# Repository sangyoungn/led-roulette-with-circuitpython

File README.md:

# LED Roulette with CircuitPython

This is a project to build an LED roulette with CircuitPython on EFR32xG24 Explorer Kit.

## Contents

"**hardware**" directory contains files for the hardware design including schematic and gerber output.
"**code**" directry contains scripts written in CircuitPython, which run on EFR32xG24 Explorer Kit.

## Directory Structure

.   
├── **hardware**   
|&nbsp;&nbsp;&nbsp;&nbsp;&nbsp;└── **roulette** (KiCad Design Directory)   
|&nbsp;&nbsp;&nbsp;&nbsp;&nbsp;&nbsp;&nbsp;&nbsp;&nbsp;&nbsp;├── **gerber** (PCB Gerber Plot Directory)   
|&nbsp;&nbsp;&nbsp;&nbsp;&nbsp;&nbsp;&nbsp;&nbsp;&nbsp;&nbsp;├── **pdf** (PCB PDF Polt Directory)   
|&nbsp;&nbsp;&nbsp;&nbsp;&nbsp;&nbsp;&nbsp;&nbsp;&nbsp;&nbsp;├── *roulette.dxf* (PCB Outline and Decoration Silk DXF)   
|&nbsp;&nbsp;&nbsp;&nbsp;&nbsp;&nbsp;&nbsp;&nbsp;&nbsp;&nbsp;├── *roulette.kicad_pcb* (PCB Design File)   
|&nbsp;&nbsp;&nbsp;&nbsp;&nbsp;&nbsp;&nbsp;&nbsp;&nbsp;&nbsp;├── *roulette.kicad_pro* (KiCad Project File)   
|&nbsp;&nbsp;&nbsp;&nbsp;&nbsp;&nbsp;&nbsp;&nbsp;&nbsp;&nbsp;├── *roulette.pdf* (PDF Plot File of Whole Schematic)   
|&nbsp;&nbsp;&nbsp;&nbsp;&nbsp;&nbsp;&nbsp;&nbsp;&nbsp;&nbsp;├── *roulette.kicad_sch* (Schematic File #1)   
|&nbsp;&nbsp;&nbsp;&nbsp;&nbsp;&nbsp;&nbsp;&nbsp;&nbsp;&nbsp;├── *LEDs.kicad_sch* (Schematic File #2)    
|&nbsp;&nbsp;&nbsp;&nbsp;&nbsp;&nbsp;&nbsp;&nbsp;&nbsp;&nbsp;└── *xg24_explorer_kit.kicad_sch* (Schematic File #3)   
└── **code**   
&nbsp;&nbsp;&nbsp;&nbsp;&nbsp;├── *code.py*   
&nbsp;&nbsp;&nbsp;&nbsp;&nbsp;└── *led_roulette.py*   

Refer to clips in the link for more information.

https://youtube.com/playlist?list=PLlT0qmKc0_5ddENmn3fNbMIVXvFqQTv2Z&si=PHfeczIfOtfNPaJ8

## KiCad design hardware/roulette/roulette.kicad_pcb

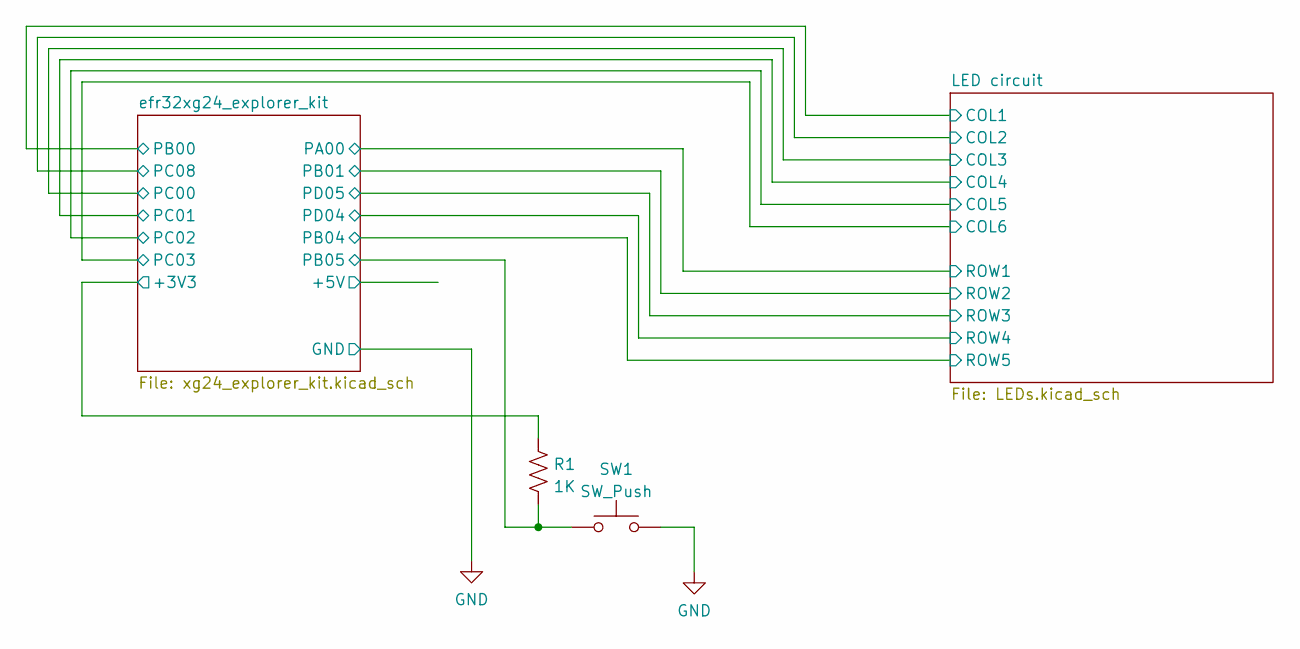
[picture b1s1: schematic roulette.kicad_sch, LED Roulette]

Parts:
R1: 1K; R_Axial_DIN0207_L6.3mm_D2.5mm_P7.62mm_Horizontal
SW1: SW_Push; SW_PUSH_6mm

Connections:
+3V3: R1.1; also elsewhere on the board
/efr32xg24_explorer_kit/PB05: R1.2, SW1.1; also elsewhere on the board
GND: SW1.2; also elsewhere on the board

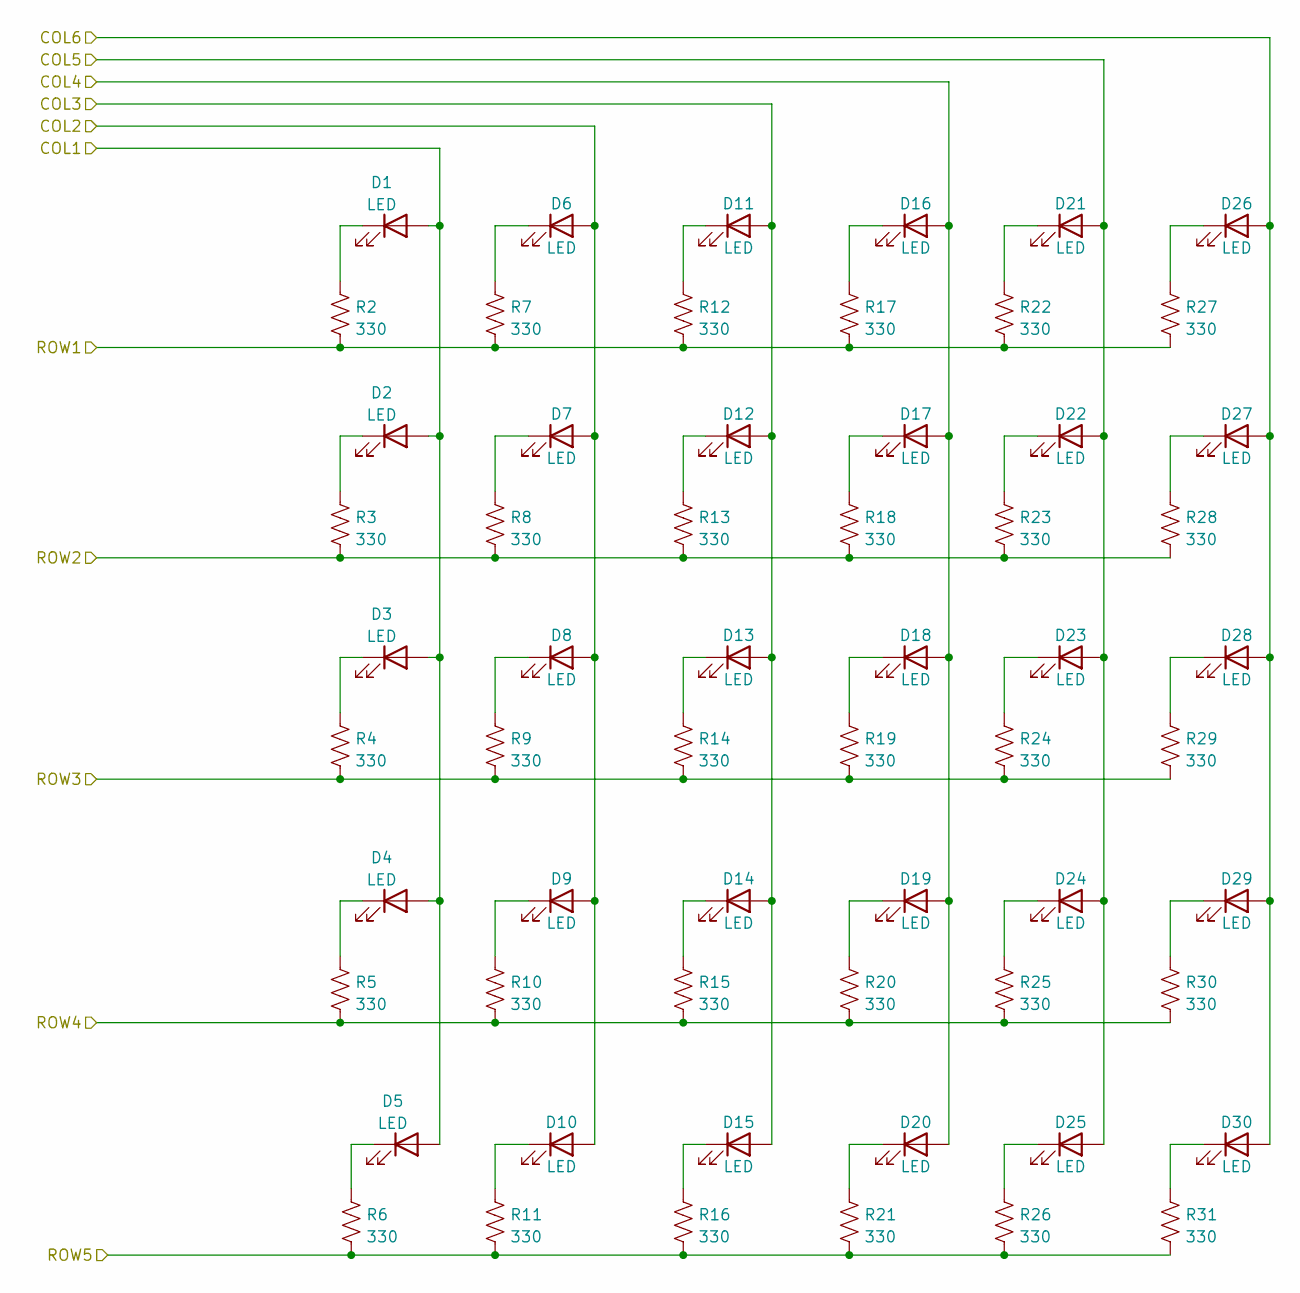
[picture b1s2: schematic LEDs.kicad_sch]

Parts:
D1, D2, D3, D4, D5, D6, D7, D8, D9, D10, D11, D12, D13, D14, D15, D16, D17, D18, D19, D20, D21, D22, D23, D24, D25, D26, D27, D28, D29, D30: LED; LED_D5.0mm
R2, R3, R4, R5, R6, R7, R8, R9, R10, R11, R12, R13, R14, R15, R16, R17, R18, R19, R20, R21, R22, R23, R24, R25, R26, R27, R28, R29, R30, R31: 330; R_Axial_DIN0207_L6.3mm_D2.5mm_P7.62mm_Horizontal

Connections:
/efr32xg24_explorer_kit/PA00: R2.2, R7.2, R12.2, R17.2, R22.2, R27.2; also elsewhere on the board
/efr32xg24_explorer_kit/PB00: D1.2 (A), D2.2 (A), D3.2 (A), D4.2 (A), D5.2 (A); also elsewhere on the board
/efr32xg24_explorer_kit/PB01: R3.2, R8.2, R13.2, R18.2, R23.2, R28.2; also elsewhere on the board
/efr32xg24_explorer_kit/PB04: R6.2, R11.2, R16.2, R21.2, R26.2, R31.2; also elsewhere on the board
/efr32xg24_explorer_kit/PC00: D11.2 (A), D12.2 (A), D13.2 (A), D14.2 (A), D15.2 (A); also elsewhere on the board
/efr32xg24_explorer_kit/PC01: D16.2 (A), D17.2 (A), D18.2 (A), D19.2 (A), D20.2 (A); also elsewhere on the board
/efr32xg24_explorer_kit/PC02: D21.2 (A), D22.2 (A), D23.2 (A), D24.2 (A), D25.2 (A); also elsewhere on the board
/efr32xg24_explorer_kit/PC03: D26.2 (A), D27.2 (A), D28.2 (A), D29.2 (A), D30.2 (A); also elsewhere on the board
/efr32xg24_explorer_kit/PC08: D6.2 (A), D7.2 (A), D8.2 (A), D9.2 (A), D10.2 (A); also elsewhere on the board
/efr32xg24_explorer_kit/PD04: R5.2, R10.2, R15.2, R20.2, R25.2, R30.2; also elsewhere on the board
/efr32xg24_explorer_kit/PD05: R4.2, R9.2, R14.2, R19.2, R24.2, R29.2; also elsewhere on the board
unnamed: D1.1 (K), R2.1
unnamed: D2.1 (K), R3.1
unnamed: D3.1 (K), R4.1
unnamed: D4.1 (K), R5.1
unnamed: D5.1 (K), R6.1
unnamed: D6.1 (K), R7.1
unnamed: D7.1 (K), R8.1
unnamed: D8.1 (K), R9.1
unnamed: D9.1 (K), R10.1
unnamed: D10.1 (K), R11.1
unnamed: D11.1 (K), R12.1
unnamed: D12.1 (K), R13.1
unnamed: D13.1 (K), R14.1
unnamed: D14.1 (K), R15.1
unnamed: D15.1 (K), R16.1
unnamed: D16.1 (K), R17.1
unnamed: D17.1 (K), R18.1
unnamed: D18.1 (K), R19.1
unnamed: D19.1 (K), R20.1
unnamed: D20.1 (K), R21.1
unnamed: D21.1 (K), R22.1
unnamed: D22.1 (K), R23.1
unnamed: D23.1 (K), R24.1
unnamed: D24.1 (K), R25.1
unnamed: D25.1 (K), R26.1
unnamed: D26.1 (K), R27.1
unnamed: D27.1 (K), R28.1
unnamed: D28.1 (K), R29.1
unnamed: D29.1 (K), R30.1
unnamed: D30.1 (K), R31.1

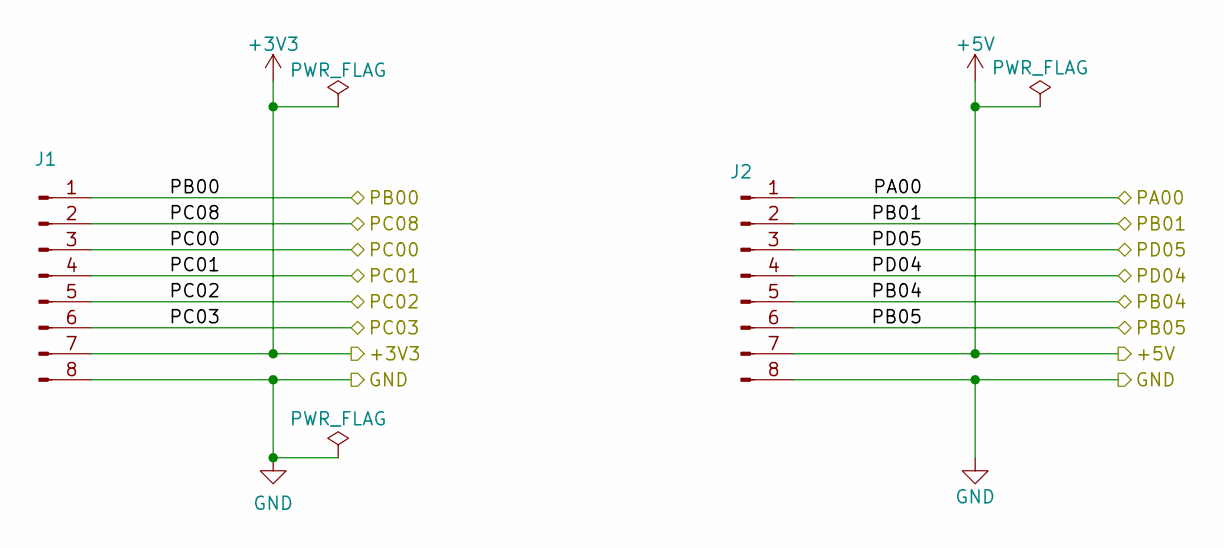
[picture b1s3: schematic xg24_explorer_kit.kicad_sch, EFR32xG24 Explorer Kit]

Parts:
J1, J2: Conn_01x08_Male; PinHeader_1x08_P2.54mm_Vertical

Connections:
+3V3: J1.7; also elsewhere on the board
+5V: J2.7
/efr32xg24_explorer_kit/PA00: J2.1; also elsewhere on the board
/efr32xg24_explorer_kit/PB00: J1.1; also elsewhere on the board
/efr32xg24_explorer_kit/PB01: J2.2; also elsewhere on the board
/efr32xg24_explorer_kit/PB04: J2.5; also elsewhere on the board
/efr32xg24_explorer_kit/PB05: J2.6; also elsewhere on the board
/efr32xg24_explorer_kit/PC00: J1.3; also elsewhere on the board
/efr32xg24_explorer_kit/PC01: J1.4; also elsewhere on the board
/efr32xg24_explorer_kit/PC02: J1.5; also elsewhere on the board
/efr32xg24_explorer_kit/PC03: J1.6; also elsewhere on the board
/efr32xg24_explorer_kit/PC08: J1.2; also elsewhere on the board
/efr32xg24_explorer_kit/PD04: J2.4; also elsewhere on the board
/efr32xg24_explorer_kit/PD05: J2.3; also elsewhere on the board
GND: J1.8, J2.8; also elsewhere on the board

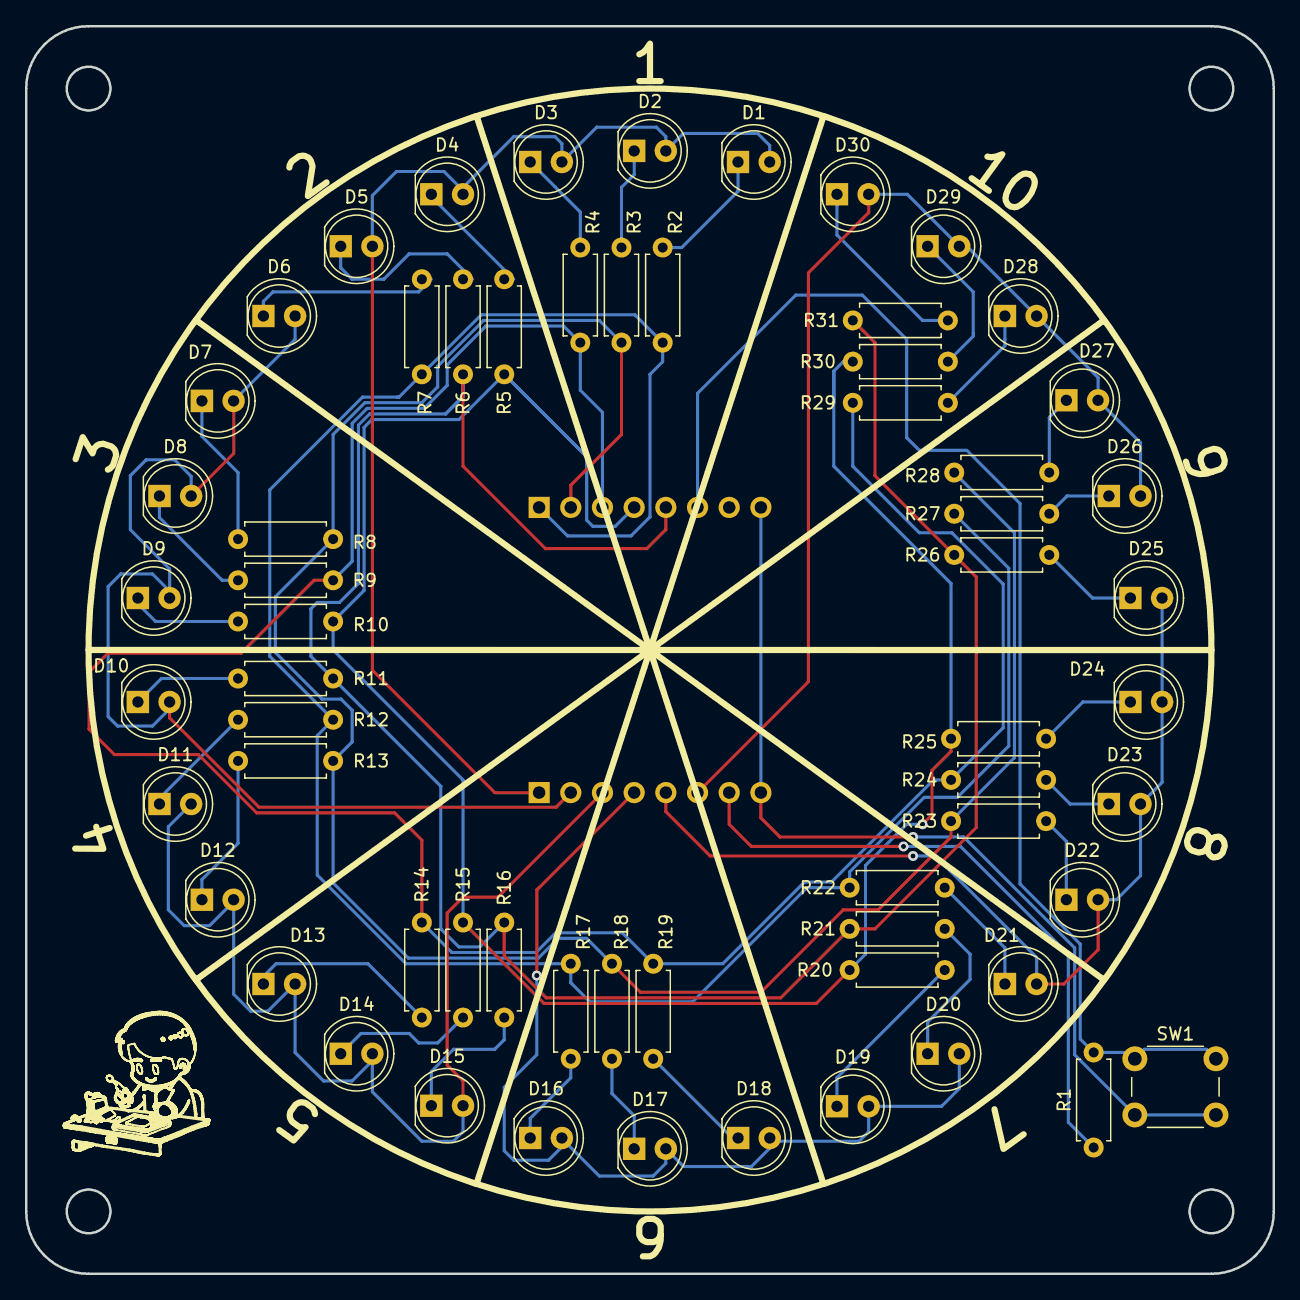
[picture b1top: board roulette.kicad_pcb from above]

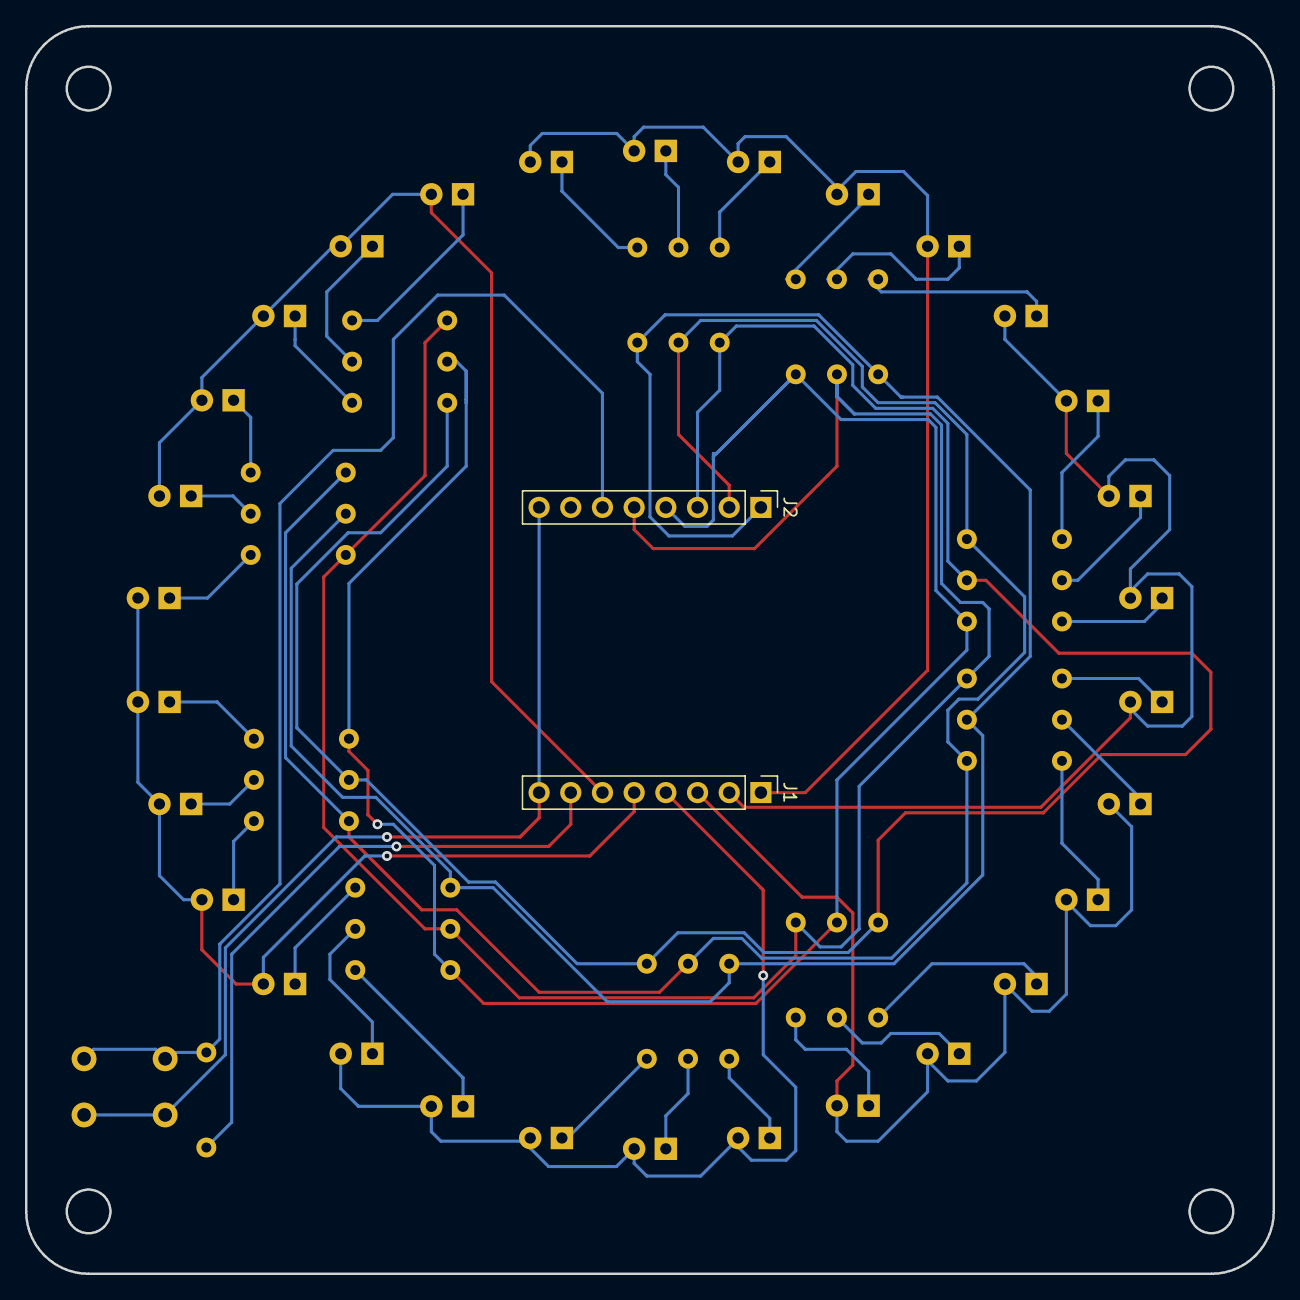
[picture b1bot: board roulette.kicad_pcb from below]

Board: 2 copper layers, 100.0 x 100.0 mm, 64 parts (2 on the bottom side), 44 nets.

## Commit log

2024-09-09 Hardware Design Work Included
2024-09-30 Added CircuitPython Code
2024-10-23 Updated README.md and added a directory asset
